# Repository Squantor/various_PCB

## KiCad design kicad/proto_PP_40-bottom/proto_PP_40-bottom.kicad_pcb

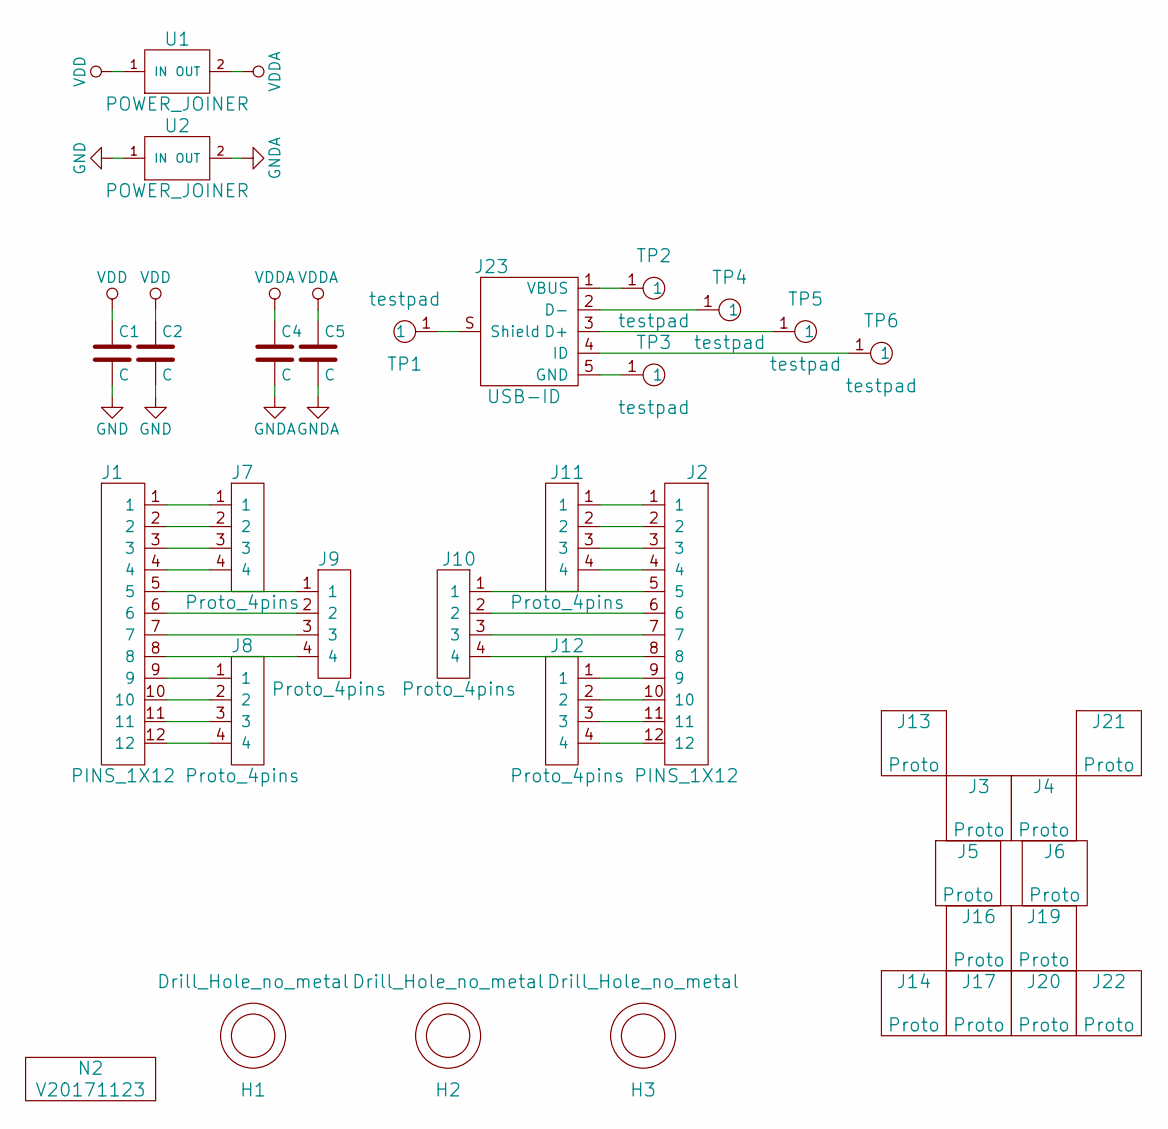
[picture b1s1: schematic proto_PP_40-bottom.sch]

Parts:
C1, C2, C4, C5: C; C_0805
H1, H2: Drill_Hole_no_metal; MountingHole_3.2mm_no_metal
H3: Drill_Hole_no_metal; MountingHole_2.2mm_no_metal
J1, J2: PINS_1X12; Header-0254-1X12-H015
J3, J4, J16, J19: Proto; proto-TH-0254-04X04-P010SQ-H008
J5, J6: Proto; proto-TH-0254-04X04-GAP02-P010SQ-H008
J7, J8, J9, J10, J11, J12: Proto_4pins; proto-TH-0254-04X01-P010SQ-H008
J13, J14, J17, J20, J21, J22: Proto; proto-SMD-0127-04X04-P010-H006
J23: USB-ID; SquantorUsb-USB-UB-SMD4H
N2: V20171123; Label_version
TP1, TP2, TP3, TP4, TP5, TP6: testpad; TESTPAD_SQ_1MM
U1, U2: POWER_JOINER; R_0402_hand

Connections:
GND: C1.2, C2.2, U2.1 (IN)
GNDA: C4.2, C5.2, U2.2 (OUT)
unnamed: J1.1, J7.1
unnamed: J1.2, J7.2
unnamed: J1.3, J7.3
unnamed: J1.4, J7.4
unnamed: J1.5, J9.1
unnamed: J1.6, J9.2
unnamed: J1.7, J9.3
unnamed: J1.8, J9.4
unnamed: J1.9, J8.1
unnamed: J1.10, J8.2
unnamed: J1.11, J8.3
unnamed: J1.12, J8.4
unnamed: J2.5, J10.1
unnamed: J2.6, J10.2
unnamed: J2.7, J10.3
unnamed: J2.8, J10.4
unnamed: J2.1, J11.1
unnamed: J2.2, J11.2
unnamed: J2.3, J11.3
unnamed: J2.4, J11.4
unnamed: J2.9, J12.1
unnamed: J2.10, J12.2
unnamed: J2.11, J12.3
unnamed: J2.12, J12.4
unnamed: J23.1 (VBUS), TP2.1
unnamed: J23.2 (D-), TP4.1
unnamed: J23.3 (D+), TP5.1
unnamed: J23.4 (ID), TP6.1
unnamed: J23.5 (GND), TP3.1
unnamed: J23.S (Shield), TP1.1
VDD: C1.1, C2.1, U1.1 (IN)
VDDA: C4.1, C5.1, U1.2 (OUT)

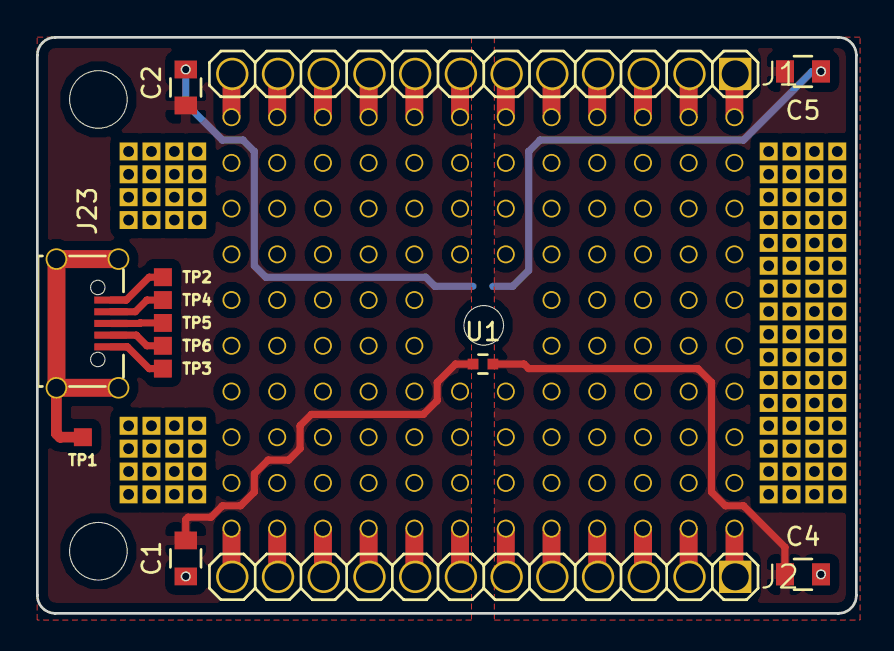
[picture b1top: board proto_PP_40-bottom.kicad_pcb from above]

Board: 2 copper layers, 45.5 x 32.0 mm, 37 parts (1 on the bottom side), 34 nets.

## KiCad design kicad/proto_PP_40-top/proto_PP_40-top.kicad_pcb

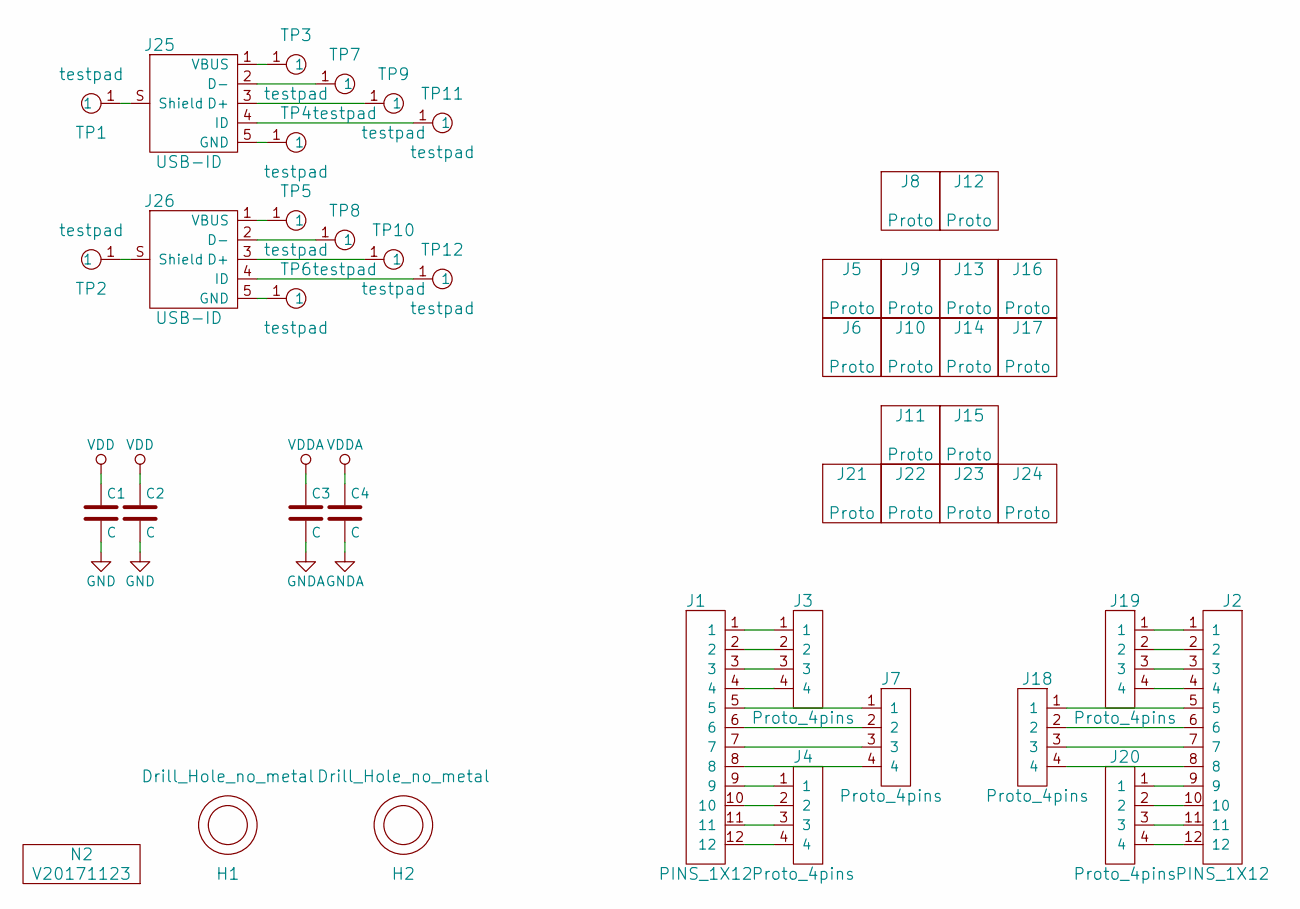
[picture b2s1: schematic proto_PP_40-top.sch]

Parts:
C1, C2, C3, C4: C; C_0805
H1, H2: Drill_Hole_no_metal; MountingHole_5.4mm_no_metal
J1, J2: PINS_1X12; Header-0254-1X12-H010
J3, J4, J7, J18, J19, J20: Proto_4pins; proto-TH-0254-04X01-P010SQ-H008
J5, J6, J9, J10, J13, J14, J16, J17, J21, J22, J23, J24: Proto; proto-SMD-0127-04X04-P010-H006
J8, J11, J12, J15: Proto; proto-TH-0254-04X04-P010SQ-H008
J25, J26: USB-ID; SquantorUsb-USB-UB-SMD4H
N2: V20171123; Label_version
TP1, TP2, TP3, TP4, TP5, TP6, TP7, TP8, TP9, TP10, TP11, TP12: testpad; TESTPAD_SQ_1MM

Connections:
GND: C1.2, C2.2
GNDA: C3.2, C4.2
unnamed: J1.1, J3.1
unnamed: J1.2, J3.2
unnamed: J1.3, J3.3
unnamed: J1.4, J3.4
unnamed: J1.5, J7.1
unnamed: J1.6, J7.2
unnamed: J1.7, J7.3
unnamed: J1.8, J7.4
unnamed: J1.9, J4.1
unnamed: J1.10, J4.2
unnamed: J1.11, J4.3
unnamed: J1.12, J4.4
unnamed: J2.9, J20.1
unnamed: J2.10, J20.2
unnamed: J2.11, J20.3
unnamed: J2.12, J20.4
unnamed: J2.5, J18.1
unnamed: J2.6, J18.2
unnamed: J2.7, J18.3
unnamed: J2.8, J18.4
unnamed: J2.1, J19.1
unnamed: J2.2, J19.2
unnamed: J2.3, J19.3
unnamed: J2.4, J19.4
unnamed: J25.1 (VBUS), TP3.1
unnamed: J25.2 (D-), TP7.1
unnamed: J25.3 (D+), TP9.1
unnamed: J25.4 (ID), TP11.1
unnamed: J25.5 (GND), TP4.1
unnamed: J25.S (Shield), TP1.1
unnamed: J26.1 (VBUS), TP5.1
unnamed: J26.2 (D-), TP8.1
unnamed: J26.3 (D+), TP10.1
unnamed: J26.4 (ID), TP12.1
unnamed: J26.5 (GND), TP6.1
unnamed: J26.S (Shield), TP2.1
VDD: C1.1, C2.1
VDDA: C3.1, C4.1

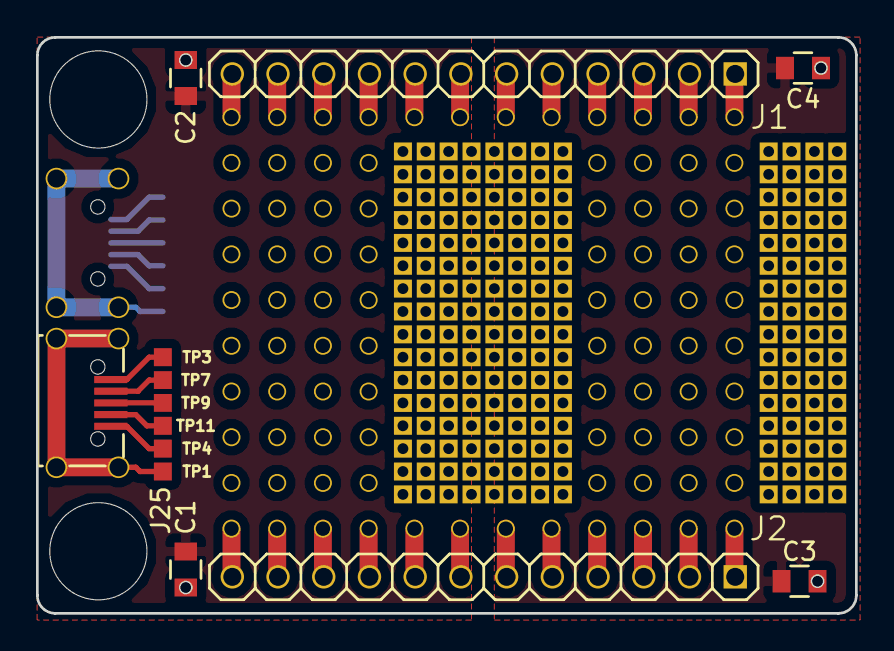
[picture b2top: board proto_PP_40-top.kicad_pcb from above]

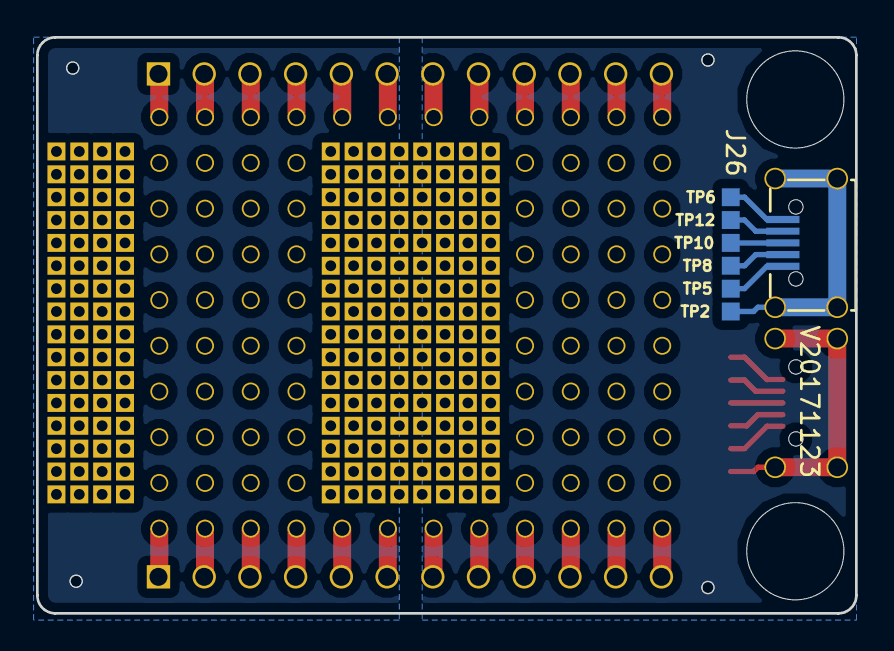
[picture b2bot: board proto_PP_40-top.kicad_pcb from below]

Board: 2 copper layers, 45.5 x 32.0 mm, 45 parts (8 on the bottom side), 40 nets.

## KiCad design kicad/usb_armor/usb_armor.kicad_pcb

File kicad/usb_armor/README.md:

# USB armor
Small circuit to protect your phone from usb hacks like like [BADUSB](https://nakedsecurity.sophos.com/2014/08/02/badusb-what-if-you-could-never-trust-a-usb-device-again/).
## TODO's
Still some things need to be done:
* Think of a project description
* schematic entry (TODO)
* PCB layout (TODO)
* Review with one night in between (TODO)
* Produce at [OSHPARK](https://oshpark.com/) (TODO)
* Assemble (TODO)
* Test & characterise (TODO)
* update Readme.md with pictures and BOM (TODO)
## BOM
The through hole microusb connector can be found from various chinese vendors.
## Pictures

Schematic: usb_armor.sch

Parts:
C1: 1u; C_0805
C2: 100n; C_0805
D1: LED; LED_D3.0mm
H1, H2: Drill_Hole_no_metal; MountingHole_2.5mm_no_metal
J1: USB; USB_A-Plug-generic
J2: USB; USB-A-TH
N1: OHWLOGO; OSHW-Symbol_6.7x6mm_SilkScreen
N2: 20190401; Label_version
R1, R2, R3, R4, R5, R6, R7, R8, R9, R10: TBD; R_0603_hand
R11: 1K; R_0603_hand

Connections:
/GND: C1.1, C2.1, D1.1, J1.4 (GND), J2.4 (GND), R4.1, R6.1, R8.1, R10.1
/IN_USB-D+: J1.3 (D+), R2.2, R5.1, R6.2
/IN_USB-D-: J1.2 (D-), R1.2, R3.1, R4.2
/OUT_USB-D+: J2.3 (D+), R2.1, R9.1, R10.2
/OUT_USB-D-: J2.2 (D-), R1.1, R7.1, R8.2
/Shield: C2.2, J1.S (Shield), J2.S (Shield)
/VBUS: C1.2, J1.1 (VBUS), J2.1 (VBUS), R3.2, R5.2, R7.2, R9.2, R11.2
unnamed: D1.2, R11.1

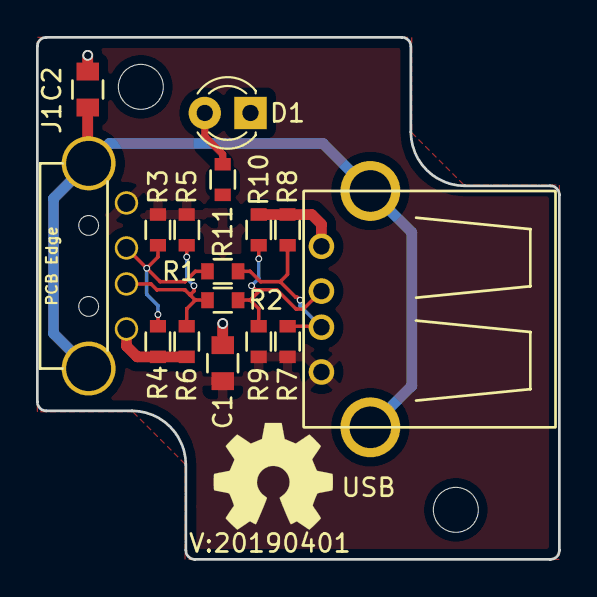
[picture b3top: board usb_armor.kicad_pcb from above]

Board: 2 copper layers, 29.0 x 29.0 mm, 20 parts (0 on the bottom side), 8 nets.

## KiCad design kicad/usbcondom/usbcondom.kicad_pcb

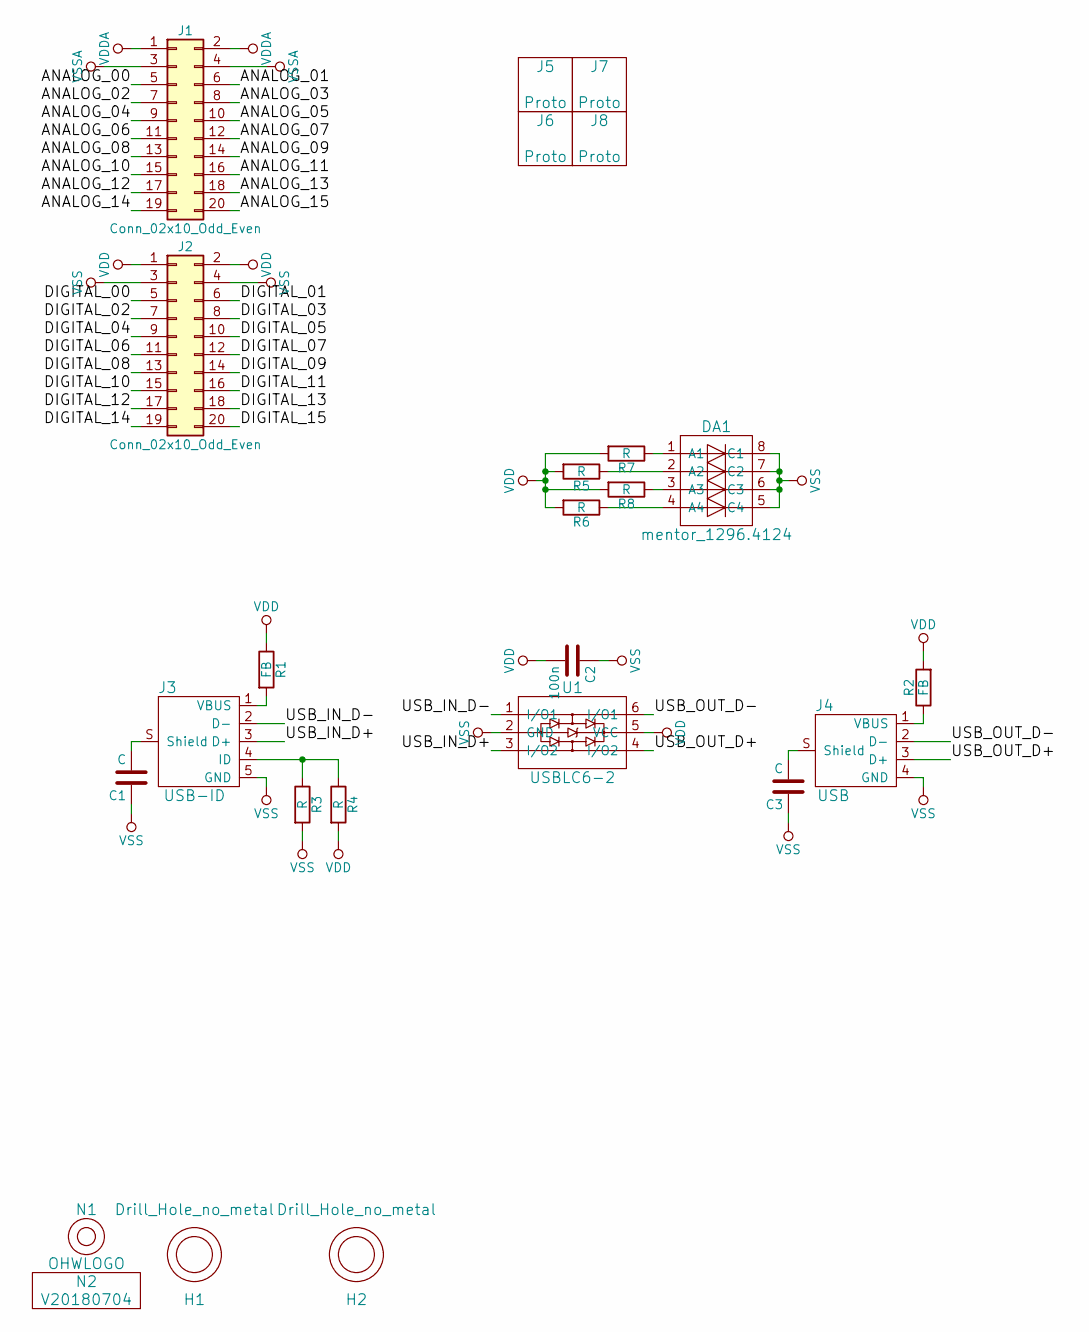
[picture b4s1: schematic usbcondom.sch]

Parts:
C1, C3: C; C_0805
C2: 100n; C_0603
DA1: mentor_1296.4124
H1, H2: Drill_Hole_no_metal; MountingHole_2.5mm_no_metal
J1, J2: Conn_02x10_Odd_Even; Header-0127-2X10-H006
J3: USB-ID; USB-muB-SMD_TH
J4: USB; USB-A-TH
J5, J6, J7, J8: Proto; proto-SMD-0127-04X04-P010-H006
N1: OHWLOGO; OSHW-Symbol_6.7x6mm_SilkScreen
N2: V20180704; Label_version
R1, R2: FB; R_0805
R3, R4, R5, R6, R7, R8: R; R_0603_hand
U1: USBLC6-2; SOT-23-6_Handsoldering

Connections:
/ANALOG_00: J1.5
/ANALOG_01: J1.6
/ANALOG_02: J1.7
/ANALOG_03: J1.8
/ANALOG_04: J1.9
/ANALOG_05: J1.10
/ANALOG_06: J1.11
/ANALOG_07: J1.12
/ANALOG_08: J1.13
/ANALOG_09: J1.14
/ANALOG_10: J1.15
/ANALOG_11: J1.16
/ANALOG_12: J1.17
/ANALOG_13: J1.18
/ANALOG_14: J1.19
/ANALOG_15: J1.20
/DIGITAL_00: J2.5
/DIGITAL_01: J2.6
/DIGITAL_02: J2.7
/DIGITAL_03: J2.8
/DIGITAL_04: J2.9
/DIGITAL_05: J2.10
/DIGITAL_06: J2.11
/DIGITAL_07: J2.12
/DIGITAL_08: J2.13
/DIGITAL_09: J2.14
/DIGITAL_10: J2.15
/DIGITAL_11: J2.16
/DIGITAL_12: J2.17
/DIGITAL_13: J2.18
/DIGITAL_14: J2.19
/DIGITAL_15: J2.20
/USB_IN_D+: J3.3 (D+), U1.3 (I/O2)
/USB_IN_D-: J3.2 (D-), U1.1 (I/O1)
/USB_OUT_D+: J4.3 (D+), U1.4 (I/O2)
/USB_OUT_D-: J4.2 (D-), U1.6 (I/O1)
unnamed: C1.2, J3.S (Shield)
unnamed: C3.2, J4.S (Shield)
unnamed: DA1.1 (A1), R7.1
unnamed: DA1.2 (A2), R5.1
unnamed: DA1.3 (A3), R8.1
unnamed: DA1.4 (A4), R6.1
unnamed: J3.1 (VBUS), R1.2
unnamed: J3.4 (ID), R3.1, R4.1
unnamed: J4.1 (VBUS), R2.1
VDD: C2.2, J2.1, J2.2, R1.1, R2.2, R4.2, R5.2, R6.2, R7.2, R8.2, U1.5 (VCC)
VDDA: J1.1, J1.2
VSS: C1.1, C2.1, C3.1, DA1.5 (C4), DA1.6 (C3), DA1.7 (C2), DA1.8 (C1), J2.3, J2.4, J3.5 (GND), J4.4 (GND), R3.2, U1.2 (GND)
VSSA: J1.3, J1.4

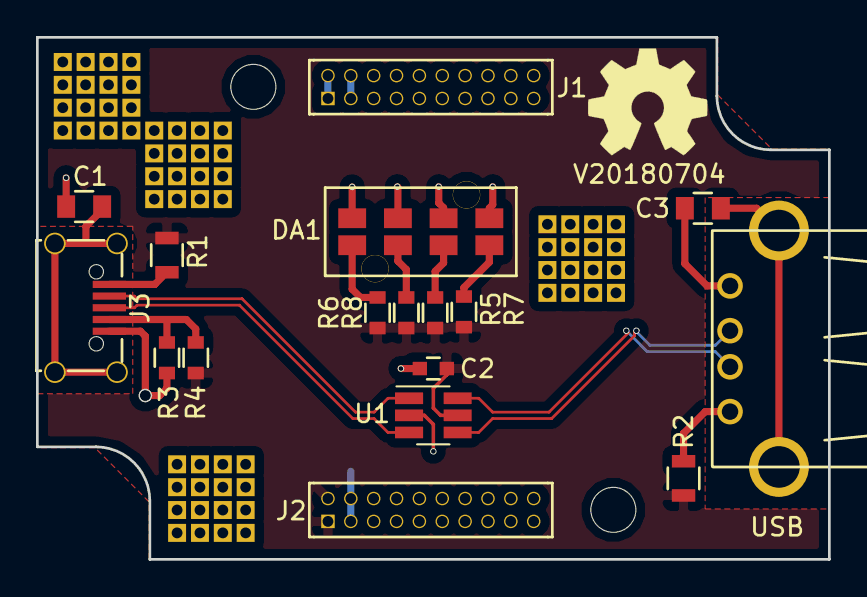
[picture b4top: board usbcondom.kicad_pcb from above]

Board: 2 copper layers, 44.0 x 29.0 mm, 25 parts (0 on the bottom side), 17 nets.
